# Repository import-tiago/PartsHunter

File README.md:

# PartsHunter

**PartsHunter** is an electronic component organization system designed for efficiency and precision. It consists of three core modules:

1. [**Windows Application**](#windows-application): A user-friendly interface for searching and managing components by description.
2. [**Hardware Device**](#hardware-device): A communication module that interacts with the Windows application to activate LEDs, pinpointing the location of each component.
3. [**Mechanical Assembly**](#mechanical-assembly): A storage system that organizes components across dedicated slots.

---
## Video - Demo

<p align="center"></p>

## How It Works
- When a search query is entered in the Windows application, an **SQLite database** is queried to retrieve relevant results.  
- The user selects the desired component(s) from the displayed results, triggering **REST requests** to the hardware device via Wi-Fi.  
- Powered by an **ESP32 web server**, the hardware processes these requests and illuminates the LEDs corresponding to the storage slots containing the selected components.  

This integrated solution streamlines component management, saving time and reducing errors in locating items.

## Flow Overview

---

## Windows Application

## Hardware Device

## Mechanical Assembly

|  |  |  |
|--|--|--|
|  |  |  |
|  |  |  |

### Contributing
0. Give this project a :star:
1. Create an issue and describe your idea.
2. [Fork it](https://github.com/import-tiago/PartsHunter/fork).
3. Create your feature branch (`git checkout -b my-new-feature`).
4. Commit your changes (`git commit -a -m "Added feature title"`).
5. Publish the branch (`git push origin my-new-feature`).
6. Create a new pull request.
7. Done! :heavy_check_mark:

<p xmlns:cc="http://creativecommons.org/ns#" xmlns:dct="http://purl.org/dc/terms/"><a property="dct:title" rel="cc:attributionURL" href="https://github.com/import-tiago/PartsHunter">PartsHunter</a> by <a rel="cc:attributionURL dct:creator" property="cc:attributionName" href="http://mailto:tiagodepaulasilva@gmail.com">Tiago Silva</a> is licensed under <a href="https://creativecommons.org/licenses/by-nc-sa/4.0/?ref=chooser-v1" target="_blank" rel="license noopener noreferrer" style="display:inline-block;">CC BY-NC-SA 4.0</a></p>

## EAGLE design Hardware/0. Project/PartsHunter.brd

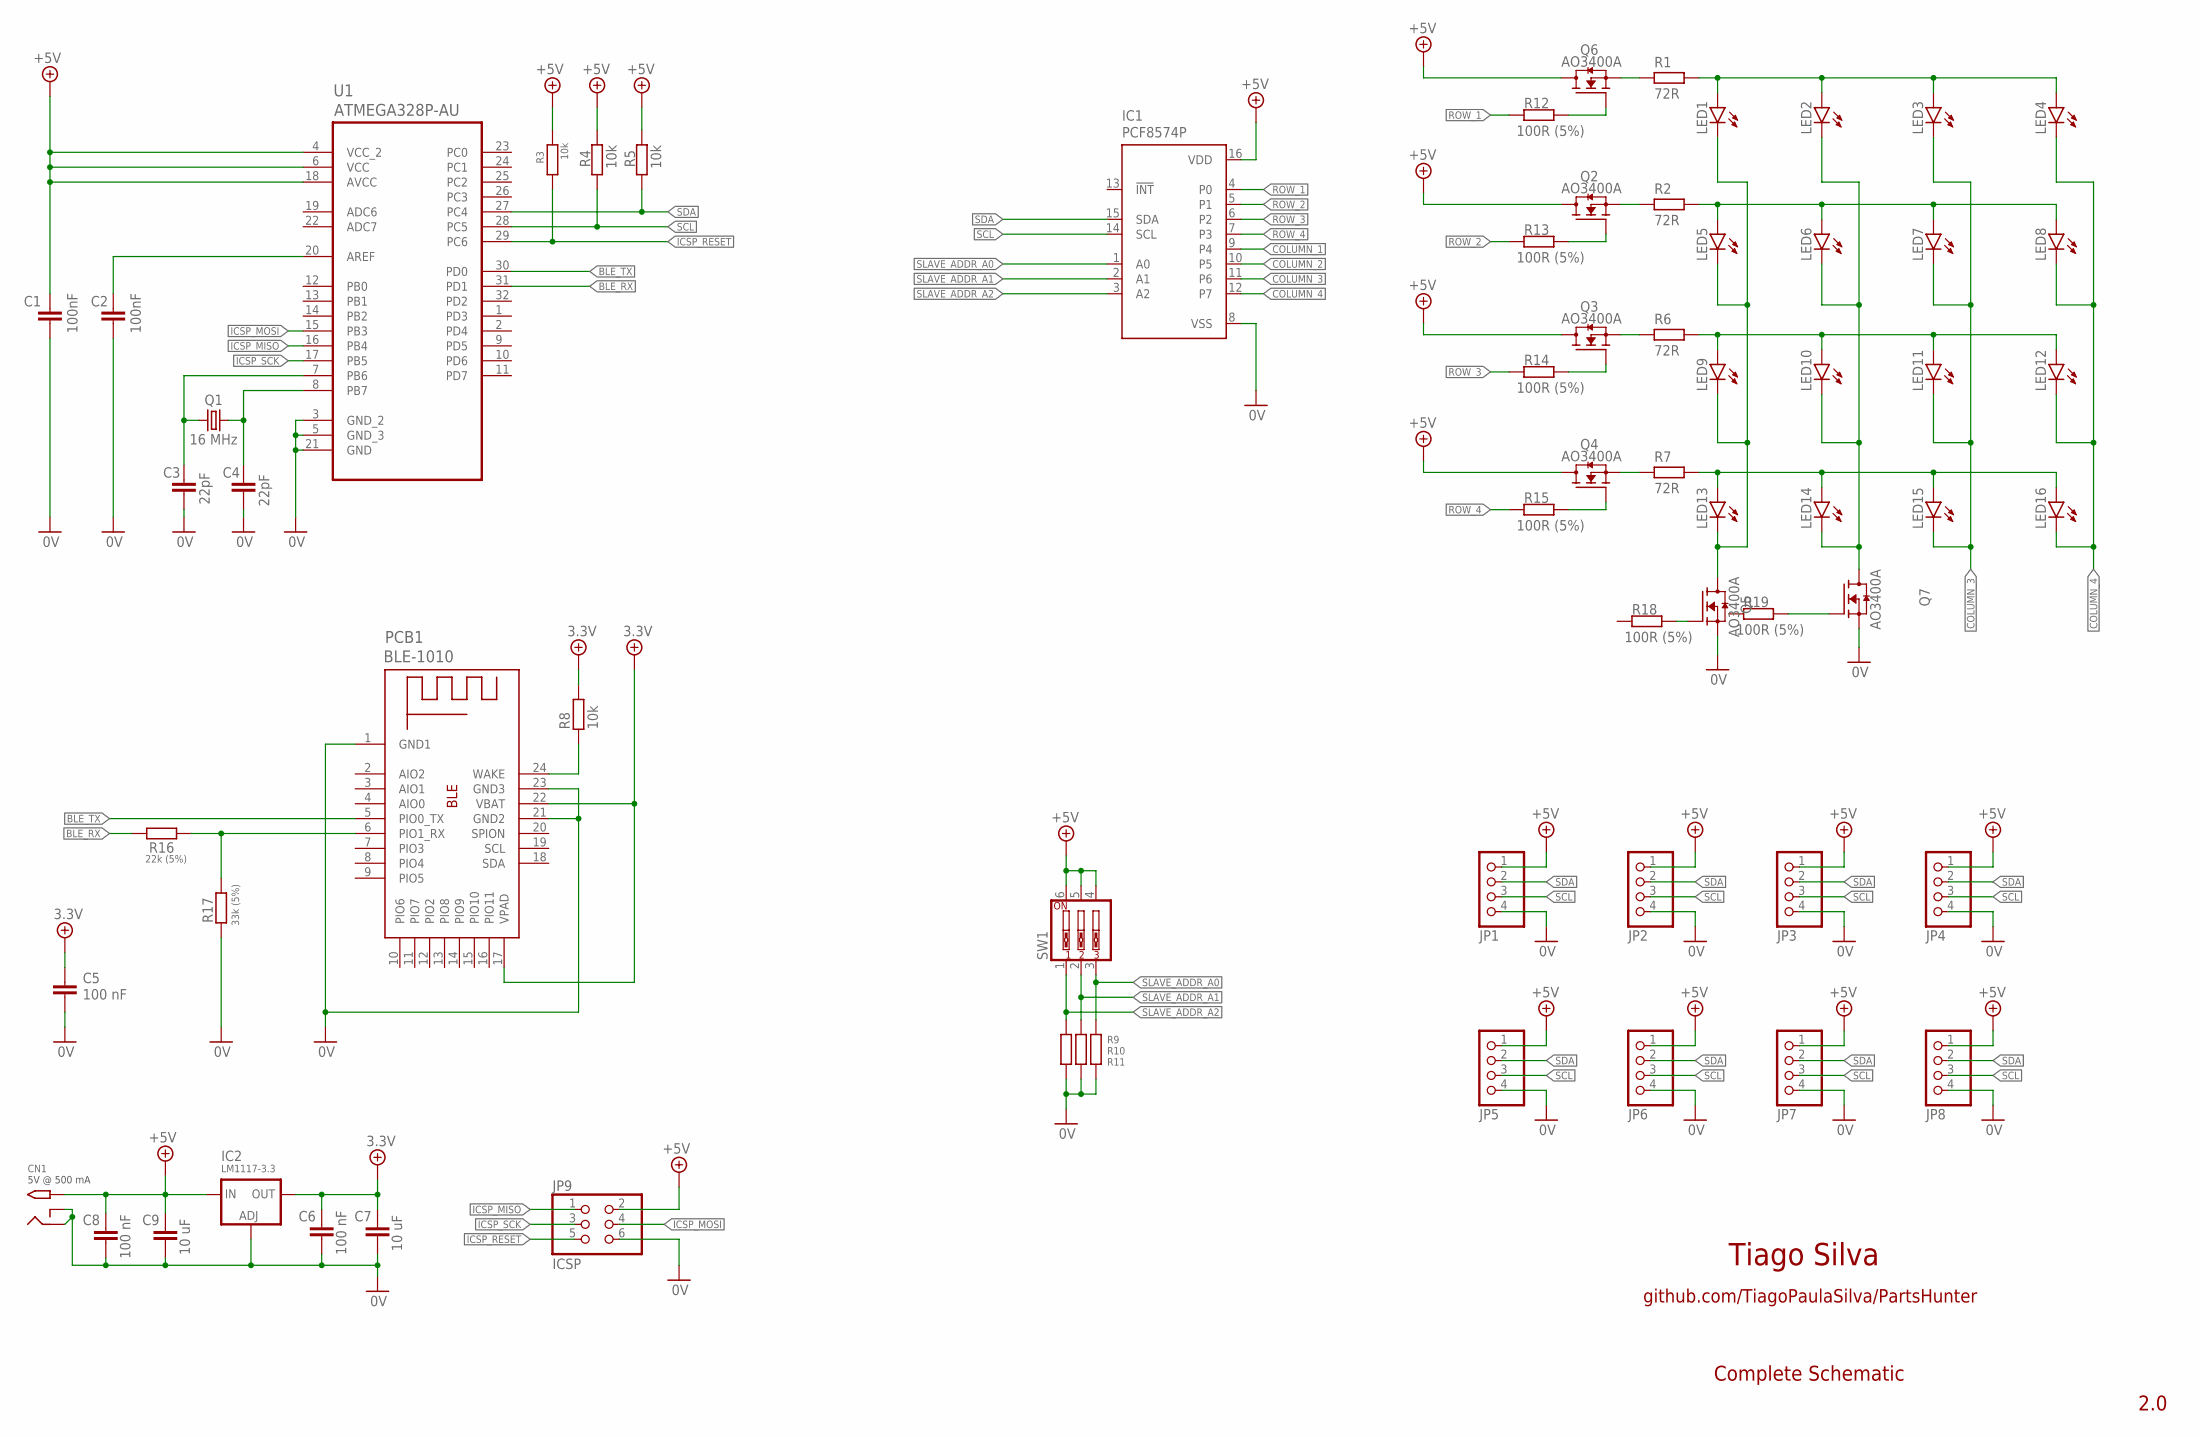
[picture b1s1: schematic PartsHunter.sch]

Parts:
C1, C2: 100nF; C0805
C3, C4: 22pF; C0805
C5, C6, C8: 100 nF; C0805
C7, C9: 10 uF; C0805
CN1: 2.1MMJACKTHM; PJ-102A
IC1: PCF8574P; DIL16
IC2: LM1117-3.3; SOT223
JP1, JP2, JP3, JP4, JP5, JP6, JP7, JP8: PINHD-1X4/90; 1X04/90
JP9: ICSP; 2X03
LED1, LED2, LED3, LED4, LED5, LED6, LED7, LED8, LED9, LED10, LED11, LED12, LED13, LED14, LED15, LED16: LEDKA-3528ASYC; KA-3528ASYC
PCB1: BLE-1010
Q1: 16 MHz; HC49UP
Q2, Q3, Q4, Q5, Q6, Q7: AO3400A; SOT95P280X125-3N
R1, R2, R6, R7: 72R; R0805
R3, R4, R5, R9, R10, R11: 10k; R0805
R8: 10k; R0603
R12, R13, R14, R15, R18, R19: 100R (5%); R0805
R16: 22k (5%); R0805
R17: 33k (5%); R0805
SW1: SW_DIP-3; EDG-03
U1: ATMEGA328P-AU; QFP80P900X900X120-32N

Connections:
0V: C1.1, C2.1, C3.1, C4.1, C5.2, C6.2, C7.2, C8.2, C9.2, CN1.RING, CN1.RING_SW, IC1.8 (VSS), IC2.1 (ADJ), JP1.4, JP2.4, JP3.4, JP4.4, JP5.4, JP6.4, JP7.4, JP8.4, JP9.6, PCB1.1 (GND1), PCB1.21 (GND2), PCB1.23 (GND3), Q5.2 (S), Q7.2 (S), R9.2, R10.2, R11.2, R17.1, U1.3 (GND_2), U1.5 (GND_3), U1.21 (GND)
3.3V: C5.1, C6.1, C7.1, IC2.4 (OUT), PCB1.17 (VPAD), PCB1.22 (VBAT), R8.1
+5V: C1.2, C8.1, C9.1, CN1.TIP, IC1.16 (VDD), IC2.3 (IN), JP1.1, JP2.1, JP3.1, JP4.1, JP5.1, JP6.1, JP7.1, JP8.1, JP9.2, Q2.3 (D), Q3.3 (D), Q4.3 (D), Q6.3 (D), R3.1, R4.1, R5.1, SW1.4, SW1.5, SW1.6, U1.4 (VCC_2), U1.6 (VCC), U1.18 (AVCC)
BLE_RX: R16.1, U1.31 (PD1)
BLE_TX: PCB1.5 (PIO0_TX), U1.30 (PD0)
BLE_WAKE: PCB1.24 (WAKE), R8.2
COLUMN_1: IC1.9 (P4), LED1.C, LED1.P$2 (C), LED5.C, LED5.P$2 (C), LED9.C, LED9.P$2 (C), LED13.C, LED13.P$2 (C), Q5.3 (D)
COLUMN_2: IC1.10 (P5), LED2.C, LED2.P$2 (C), LED6.C, LED6.P$2 (C), LED10.C, LED10.P$2 (C), LED14.C, LED14.P$2 (C), Q7.3 (D)
COLUMN_3: IC1.11 (P6), LED3.C, LED3.P$2 (C), LED7.C, LED7.P$2 (C), LED11.C, LED11.P$2 (C), LED15.C, LED15.P$2 (C)
COLUMN_4: IC1.12 (P7), LED4.C, LED4.P$2 (C), LED8.C, LED8.P$2 (C), LED12.C, LED12.P$2 (C), LED16.C, LED16.P$2 (C)
ICSP_MISO: JP9.1, U1.16 (PB4)
ICSP_MOSI: JP9.4, U1.15 (PB3)
ICSP_RESET: JP9.5, R3.2, U1.29 (PC6)
ICSP_SCK: JP9.3, U1.17 (PB5)
unnamed: C3.2, Q1.1, U1.7 (PB6)
unnamed: C4.2, Q1.2, U1.8 (PB7)
unnamed: Q6.1 (G), R12.2
unnamed: Q6.2 (S), R1.2
unnamed: LED1.A, LED1.P$1 (A), LED2.A, LED2.P$1 (A), LED3.A, LED3.P$1 (A), LED4.A, LED4.P$1 (A), R1.1
unnamed: LED5.A, LED5.P$1 (A), LED6.A, LED6.P$1 (A), LED7.A, LED7.P$1 (A), LED8.A, LED8.P$1 (A), R2.1
unnamed: LED9.A, LED9.P$1 (A), LED10.A, LED10.P$1 (A), LED11.A, LED11.P$1 (A), LED12.A, LED12.P$1 (A), R6.1
unnamed: LED13.A, LED13.P$1 (A), LED14.A, LED14.P$1 (A), LED15.A, LED15.P$1 (A), LED16.A, LED16.P$1 (A), R7.1
unnamed: Q4.1 (G), R15.2
unnamed: Q2.2 (S), R2.2
unnamed: Q3.1 (G), R14.2
unnamed: Q3.2 (S), R6.2
unnamed: Q2.1 (G), R13.2
unnamed: Q4.2 (S), R7.2
unnamed: PCB1.6 (PIO1_RX), R16.2, R17.2
unnamed: Q5.1 (G), R18.2
unnamed: C2.2, U1.20 (AREF)
unnamed: Q7.1 (G), R19.2
ROW_1: IC1.4 (P0), R12.1
ROW_2: IC1.5 (P1), R13.1
ROW_3: IC1.6 (P2), R14.1
ROW_4: IC1.7 (P3), R15.1
SCL: IC1.14 (SCL), JP1.3, JP2.3, JP3.3, JP4.3, JP5.3, JP6.3, JP7.3, JP8.3, R4.2, U1.28 (PC5)
SDA: IC1.15 (SDA), JP1.2, JP2.2, JP3.2, JP4.2, JP5.2, JP6.2, JP7.2, JP8.2, R5.2, U1.27 (PC4)
SLAVE_ADDR_A0: IC1.1 (A0), R11.1, SW1.3
SLAVE_ADDR_A1: IC1.2 (A1), R10.1, SW1.2
SLAVE_ADDR_A2: IC1.3 (A2), R9.1, SW1.1

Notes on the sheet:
Tiago Silva
github.com/TiagoPaulaSilva/PartsHunter
2.0
Complete Schematic
5V @ 500 mA

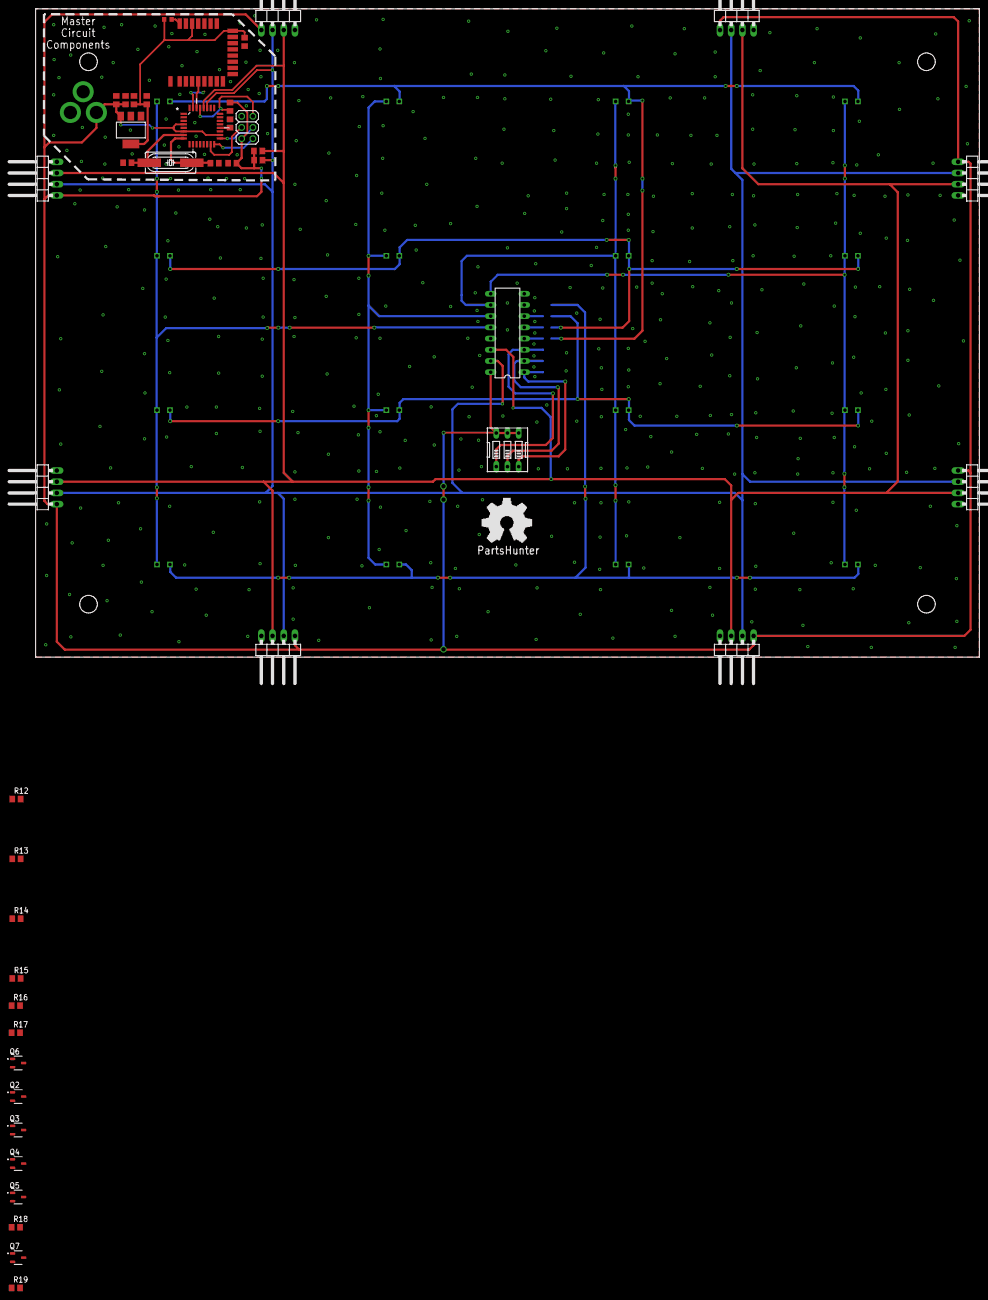
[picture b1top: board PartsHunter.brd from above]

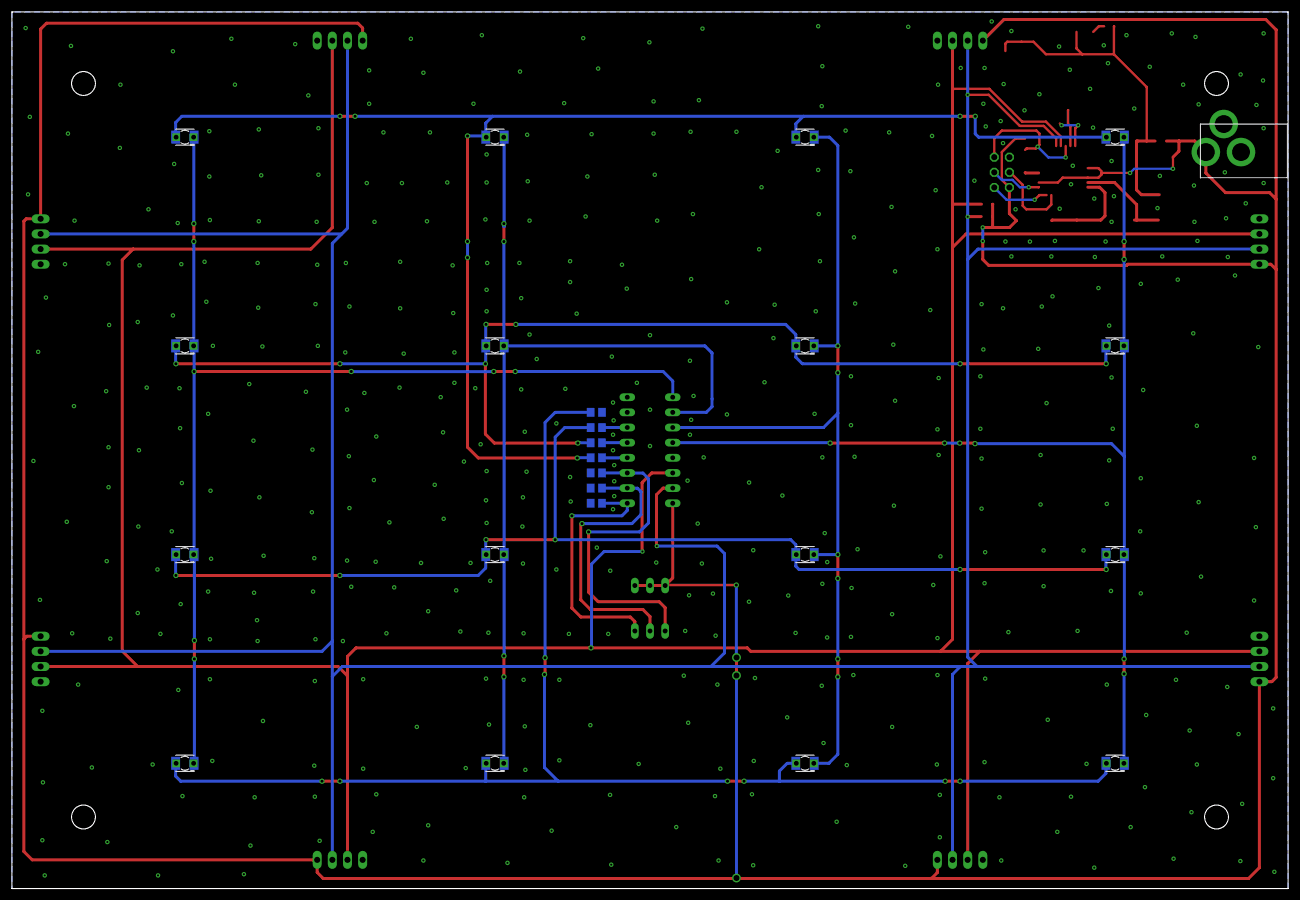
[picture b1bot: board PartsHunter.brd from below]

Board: 2 copper layers, 214.0 x 147.0 mm, 66 parts (24 on the bottom side), 41 nets.

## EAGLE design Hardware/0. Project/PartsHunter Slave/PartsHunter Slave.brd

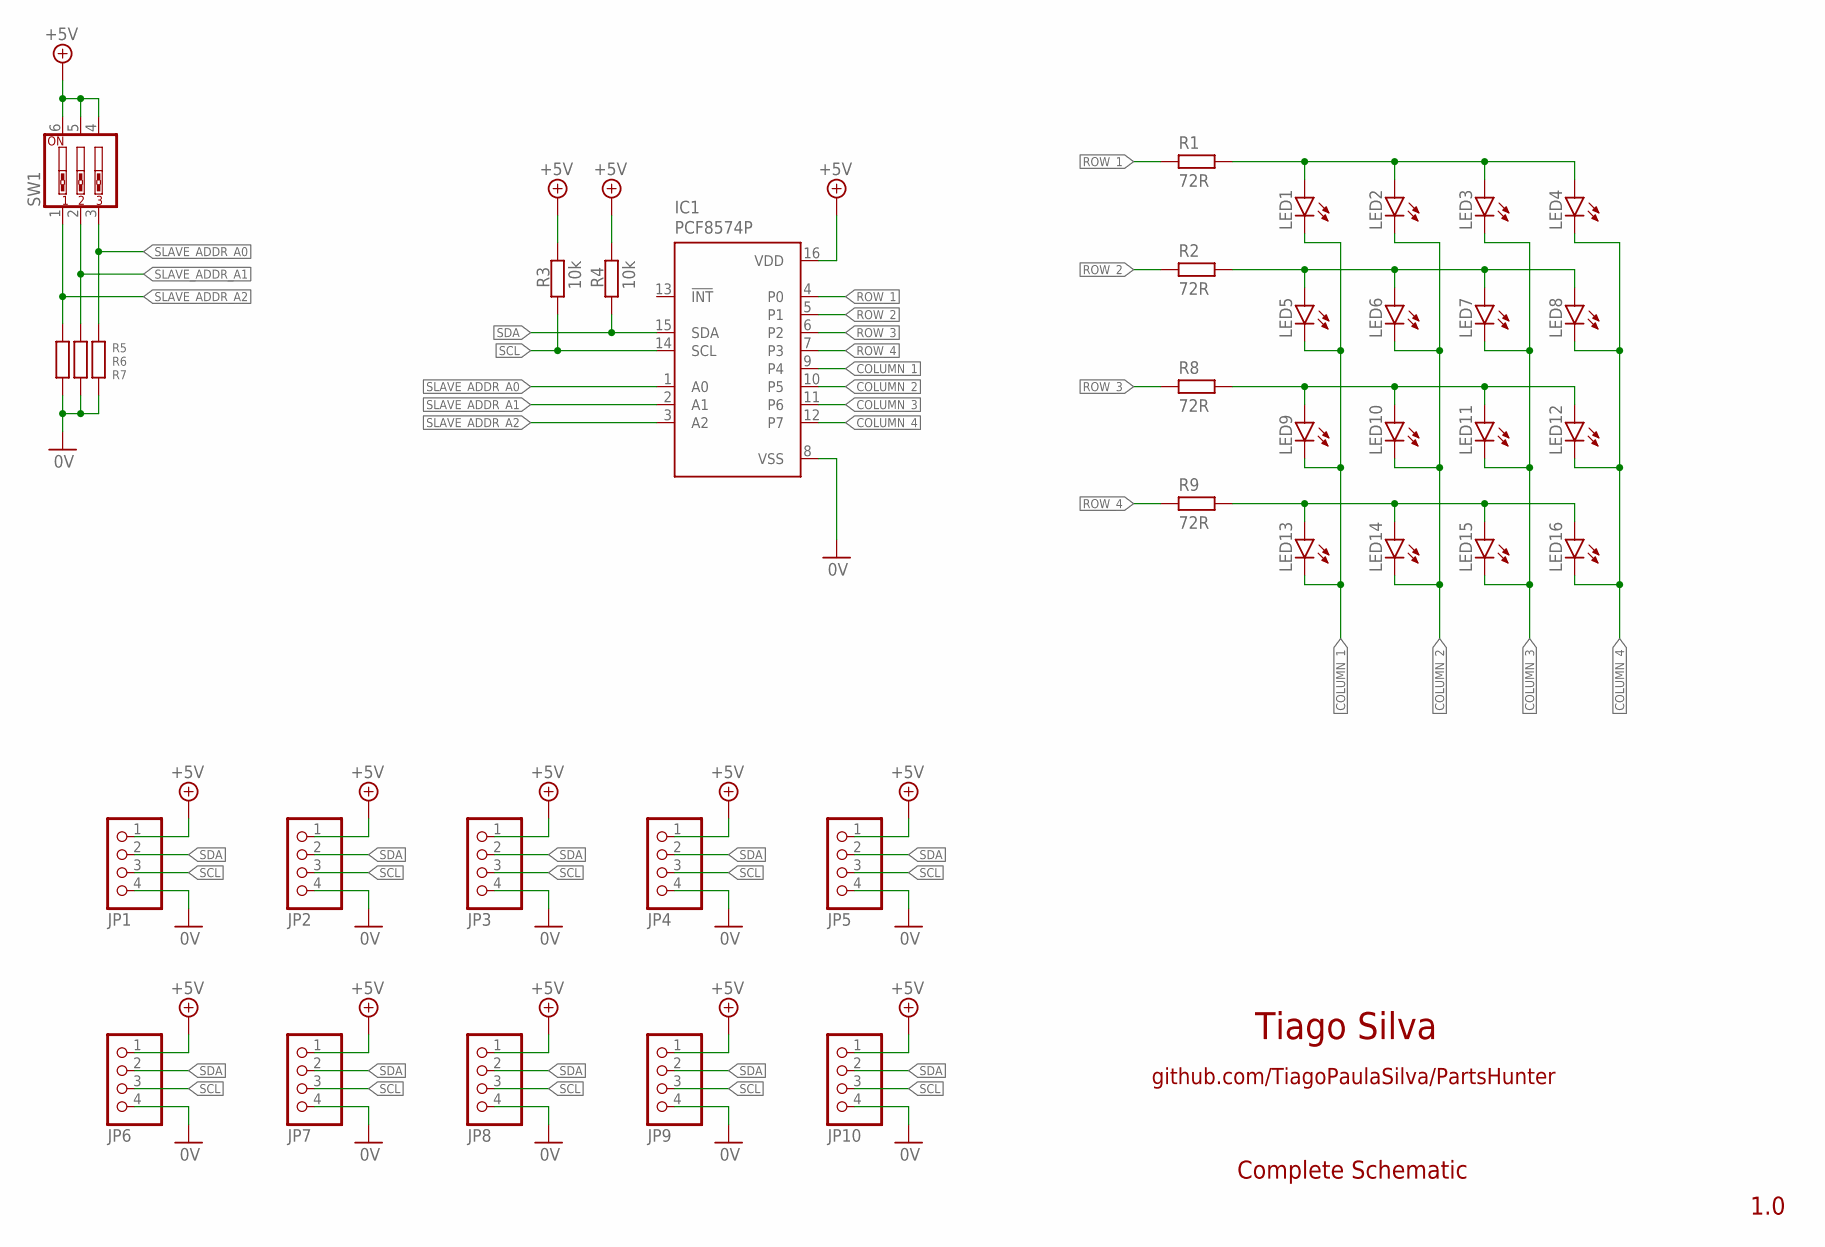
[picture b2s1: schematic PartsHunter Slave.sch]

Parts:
IC1: PCF8574P; DIL16
JP1, JP2, JP3, JP4, JP6, JP7, JP8, JP9: PINHD-1X4/90; 1X04/90
JP5, JP10: PINHD-1X4; 1X04
LED1, LED2, LED3, LED4, LED5, LED6, LED7, LED8, LED9, LED10, LED11, LED12, LED13, LED14, LED15, LED16: LEDKA-3528ASYC; KA-3528ASYC
R1, R2, R8, R9: 72R; R0805
R3, R4, R5, R6, R7: 10k; R0805
SW1: SW_DIP-3; EDG-03

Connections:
0V: IC1.8 (VSS), JP1.4, JP2.4, JP3.4, JP4.4, JP5.4, JP6.4, JP7.4, JP8.4, JP9.4, JP10.4, R5.2, R6.2, R7.2
+5V: IC1.16 (VDD), JP1.1, JP2.1, JP3.1, JP4.1, JP5.1, JP6.1, JP7.1, JP8.1, JP9.1, JP10.1, R3.1, R4.1, SW1.4, SW1.5, SW1.6
COLUMN_1: IC1.9 (P4), LED1.C, LED5.C, LED9.C, LED13.C
COLUMN_2: IC1.10 (P5), LED2.C, LED6.C, LED10.C, LED14.C
COLUMN_3: IC1.11 (P6), LED3.C, LED7.C, LED11.C, LED15.C
COLUMN_4: IC1.12 (P7), LED4.C, LED8.C, LED12.C, LED16.C
unnamed: LED1.A, LED2.A, LED3.A, LED4.A, R1.1
unnamed: LED5.A, LED6.A, LED7.A, LED8.A, R2.1
unnamed: LED9.A, LED10.A, LED11.A, LED12.A, R8.1
unnamed: LED13.A, LED14.A, LED15.A, LED16.A, R9.1
ROW_1: IC1.4 (P0), R1.2
ROW_2: IC1.5 (P1), R2.2
ROW_3: IC1.6 (P2), R8.2
ROW_4: IC1.7 (P3), R9.2
SCL: IC1.14 (SCL), JP1.3, JP2.3, JP3.3, JP4.3, JP5.3, JP6.3, JP7.3, JP8.3, JP9.3, JP10.3, R3.2
SDA: IC1.15 (SDA), JP1.2, JP2.2, JP3.2, JP4.2, JP5.2, JP6.2, JP7.2, JP8.2, JP9.2, JP10.2, R4.2
SLAVE_ADDR_A0: IC1.1 (A0), R7.1, SW1.3
SLAVE_ADDR_A1: IC1.2 (A1), R6.1, SW1.2
SLAVE_ADDR_A2: IC1.3 (A2), R5.1, SW1.1

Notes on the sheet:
Tiago Silva
github.com/TiagoPaulaSilva/PartsHunter
1.0
Complete Schematic

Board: 2 copper layers, 37 parts (25 on the bottom side), 19 nets, no tracks yet.

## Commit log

2019-08-31 Slave's schematic done
2019-08-31 I2C to GPIO datasheet added
2019-08-31 Slave's PCB layout done
2019-09-01 rearranged components positions at PCB layout
2019-09-01 Hardware project finished
2019-09-01 Add gerbers files
2019-09-01 Arduino Pro Mini Pinout Reference Added
2019-09-02 File names changed
2019-09-02 Gerber files generated
2019-09-02 I2C pull-ups moved to master's circuit area
2019-09-03 New datasheet added
2019-09-10 SMD and PTH led option added
2019-11-16 Added new images
2020-01-26 Working on 2.0 PCB (bug fix)
2020-01-28 gitattributes created
2020-12-21 3D Models added
2020-12-21 Drawer's LED controlled by ESP UART
2020-12-25 .gitignore removed
2020-12-25 New directories structure
2020-12-25 New images assets adeed
2020-12-27 refactoring variables
2020-12-27 New images added
2020-12-27 .gitignore added to protect App.config file
2020-12-27 Minor improvements
2020-12-29 Button Add New Box working properly
2021-01-05 Firmware working properly - DONE
2021-01-05 PC UART and MCU UART working properly
2021-01-05 Added no blinky (always on) LED feature
2021-01-05 LED-strip highlight from Register tab
2021-01-06 Part delete feature added
2021-01-06 Buttons Edit and Delete added and working properly
2021-01-21 Reduction in filament consumption
2021-03-08 Before Firebase
2021-03-08 Firebase WIP
2021-03-09 Firebase and UART commands working properly
2021-03-09 Firmware + Windows App + Firebase working properly
2021-03-09 New .gitignore
2021-03-09 First Publish
2021-03-09 PartsHunter 1.0.0.8 realease
2021-03-10 PartsHunter 1.0.0.10 realease
2021-03-10 PartsHunter 1.0.0.11 realease
2021-03-10 PartsHunter 1.0.0.12 realease
2021-03-10 PartsHunter 1.0.0.13 realease
2021-03-12 Mobile app init
2021-03-12 Mobile app connected to Firebase and new Flutter template at gitignore
2021-03-13 Get from Firebase and fill ListView working properly
2021-03-16 DataTable + Firebase working properly
2021-03-16 Search by description working properly
2021-03-16 Keypad screen added and connected to Firebase and hardware device
2021-03-19 New edit/delete buttons
2021-03-19 Mobile app finished
2021-03-24 Keyboard input at Drawer textBox is now only numbers
2021-03-24 Added popup alert to register parts with same description
2021-03-27 Batch registration feature added
2021-03-28 My own bath-parts .txt file added
2021-03-29 Sort A->B / B->A added to datatable columns
2021-03-31 Fix a error at 1N4148 diode string
2021-04-11 New passive components added
2021-04-21 including: authenticationBusiness
2021-04-21 including: repositories (local & firebase)
2021-04-21 including: models (led & component)
2021-04-21 including: services (server
2021-04-21 maintenance: program/forms (dependency injection and architecture)
2021-04-21 maintenance: general configuration
2021-04-21 removing: controller
2021-05-19 maintenance: desing props firebaseRepository
2021-05-23 Refactoring: defining responsibility
2022-02-05 Bump RestSharp from 106.11.7 to 106.12.0 in /Windows App/PartsHunter
    Bumps [RestSharp](https://github.com/restsharp/RestSharp) from 106.11.7 to 106.12.0.
    - [Release notes](https://github.com/restsharp/RestSharp/releases)
    - [Changelog](https://github.com/restsharp/RestSharp/blob/dev/releasenotes.md)
    - [Commits](https://github.com/restsharp/RestSharp/compare/106.11.7...106.12)
    ---
    updated-dependencies:
2022-06-23 Bump Newtonsoft.Json from 12.0.3 to 13.0.1 in /Windows App/PartsHunter
    Bumps [Newtonsoft.Json](https://github.com/JamesNK/Newtonsoft.Json) from 12.0.3 to 13.0.1.
    - [Release notes](https://github.com/JamesNK/Newtonsoft.Json/releases)
    - [Commits](https://github.com/JamesNK/Newtonsoft.Json/compare/12.0.3...13.0.1)
    ---
    updated-dependencies:
    - dependency-name: Newtonsoft.Json
2022-12-08 Bump Newtonsoft.Json from 12.0.3 to 13.0.2 in /Windows App/PartsHunter
    Bumps [Newtonsoft.Json](https://github.com/JamesNK/Newtonsoft.Json) from 12.0.3 to 13.0.2.
    - [Release notes](https://github.com/JamesNK/Newtonsoft.Json/releases)
    - [Commits](https://github.com/JamesNK/Newtonsoft.Json/compare/12.0.3...13.0.2)
    ---
    updated-dependencies:
    - dependency-name: Newtonsoft.Json
2023-07-21 usernames in URLs updated
2024-11-08 added base structure
2024-11-08 added database
2024-11-08 EF Core + SQLite is working
2024-11-09 Register and Search works
2024-11-09 base firmware structure created
2024-11-09 Base Wi-Fi connection and static IP added
2024-11-09 Base WebServer added
2024-11-10 Release v1.0
2024-11-11 Migrate from async web server to non-async one
2024-11-11 brightness adj works
2024-11-12 Blink interval, brightness and color is now adjustable
2024-11-21 Update/Edit buttons works
2024-11-22 added bill of materials area to highlight multiples parts
2024-11-23 hardware device methods and http requests organized in a service class
2024-11-23 added new image
2024-11-23 ensure commit after saving data in db
2024-11-23 ensure clear pixels at form closing
2024-11-24 Ensure clear pixels when form is closing but not blocking
2024-11-24 release
2024-11-24 removed uncensored files
2024-11-24 Added video image thumbnail
2025-01-04 added tube image
2025-01-12 added 3d models images
2025-01-12 renamed images
2025-11-21 adafruit neo pixel lib updated from v1.12 to v1.15
